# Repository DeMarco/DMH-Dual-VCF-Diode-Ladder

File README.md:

# DMH-Dual-VCF-Diode-Ladder
Stereo version of DMH Diode Ladder VCF

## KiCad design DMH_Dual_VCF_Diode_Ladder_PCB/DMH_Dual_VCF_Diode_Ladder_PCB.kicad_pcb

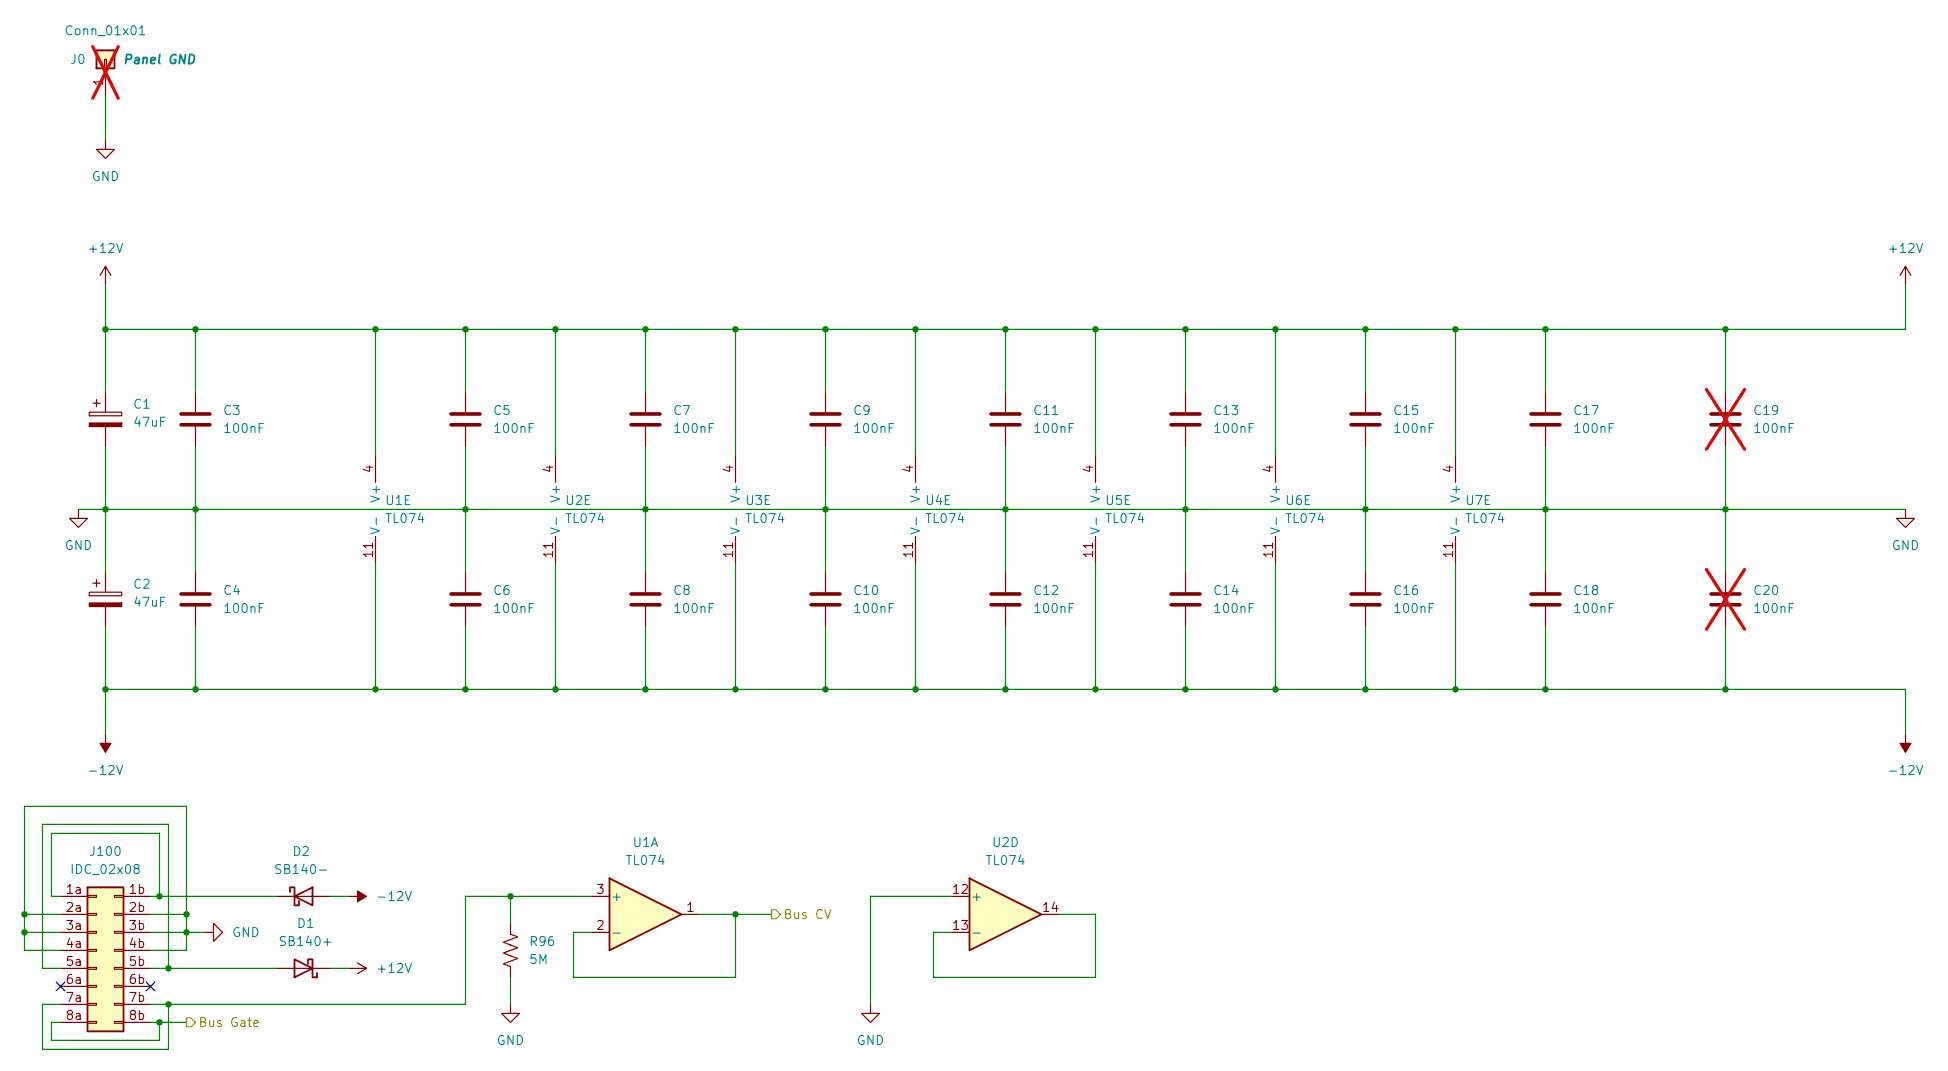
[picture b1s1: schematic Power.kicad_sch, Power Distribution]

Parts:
C1, C2: 47uF; CP_Radial_D5.0mm_P2.00mm
C3, C4, C5, C6, C7, C8, C9, C10, C11, C12, C13, C14, C15, C16, C17, C18: 100nF; C_Disc_D4.3mm_W1.9mm_P5.00mm
C19, C20: 100nF; C_Disc_D4.3mm_W1.9mm_P5.00mm; not fitted
D1: SB140+; D_DO-41_SOD81_P10.16mm_Horizontal
D2: SB140-; D_DO-41_SOD81_P10.16mm_Horizontal
J0: Conn_01x01; PinHeader_1x01_P2.54mm_Vertical; not fitted
J100: IDC_02x08; IDC-Header_2x08_P2.54mm_Vertical_Eurorack
R96: 5M; R_Axial_DIN0207_L6.3mm_D2.5mm_P7.62mm_Horizontal
U1, U2, U3, U4, U5, U6, U7: TL074; DIP-14_W7.62mm_Socket

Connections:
+12V: C1.1, C3.1, C5.1, C7.1, C9.1, C11.1, C13.1, C15.1, C17.1, C19.1, D1.1 (K), U1.4 (V+), U2.4 (V+), U3.4 (V+), U4.4 (V+), U5.4 (V+), U6.4 (V+), U7.4 (V+); also elsewhere on the board
-12V: C2.2, C4.2, C6.2, C8.2, C10.2, C12.2, C14.2, C16.2, C18.2, C20.2, D2.2 (A), U1.11 (V-), U2.11 (V-), U3.11 (V-), U4.11 (V-), U5.11 (V-), U6.11 (V-), U7.11 (V-); also elsewhere on the board
/CV Processing/Bus CV A Input: U1.1, U1.2 (-); also elsewhere on the board
/Power/Bus Gate: J100.8a, J100.8b
GND: C1.2, C2.1, C3.2, C4.1, C5.2, C6.1, C7.2, C8.1, C9.2, C10.1, C11.2, C12.1, C13.2, C14.1, C15.2, C16.1, C17.2, C18.1, C19.2, C20.1, J0.1, J100.2a, J100.2b, J100.3a, J100.3b, J100.4a, J100.4b, R96.2, U2.12 (+); also elsewhere on the board
unnamed: D1.2 (A), J100.5a, J100.5b
unnamed: D2.1 (K), J100.1a, J100.1b
unnamed: J100.7a, J100.7b, R96.1, U1.3 (+)
unnamed: U2.13 (-), U2.14

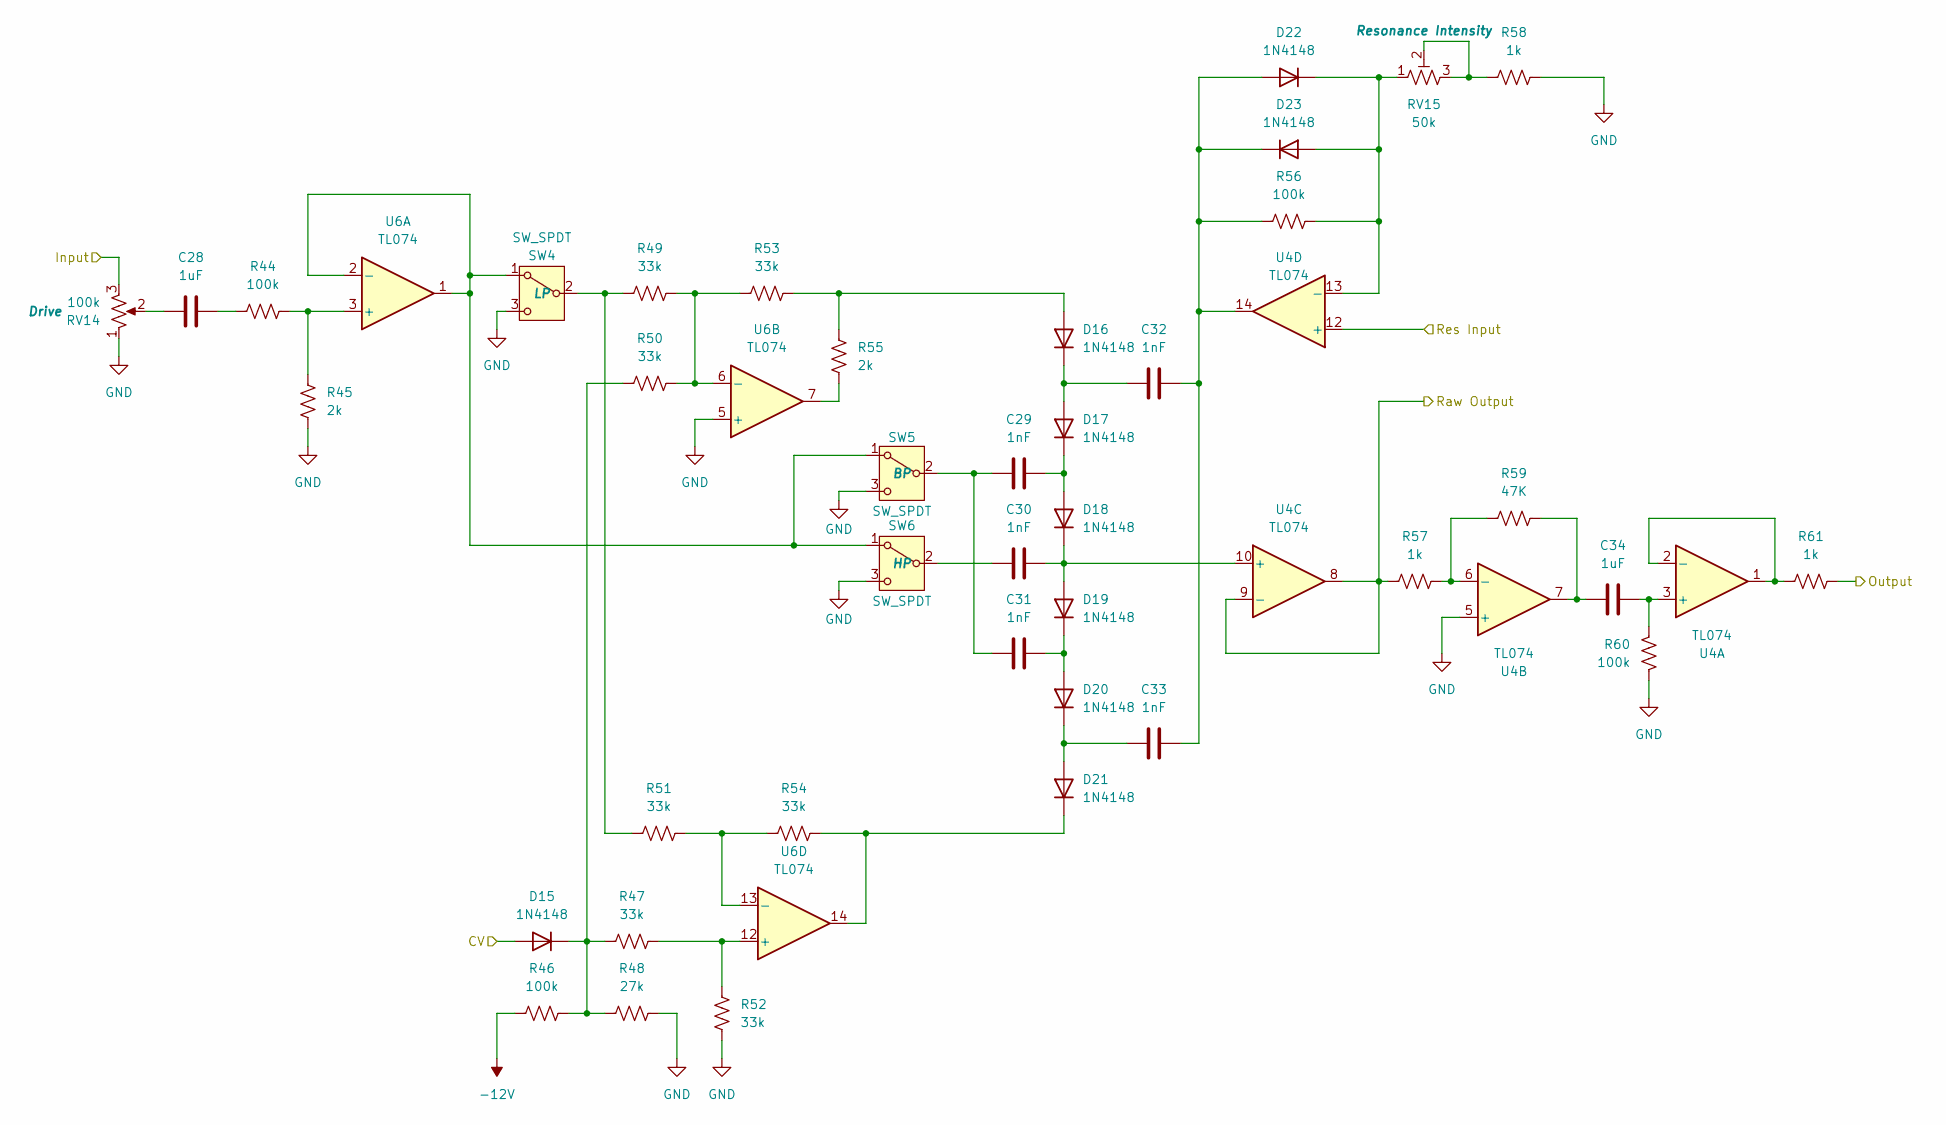
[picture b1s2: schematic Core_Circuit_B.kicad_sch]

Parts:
C28, C34: 1uF; C_Disc_D4.3mm_W1.9mm_P5.00mm
C29, C30, C31, C32, C33: 1nF; C_Disc_D4.3mm_W1.9mm_P5.00mm
D15, D16, D17, D18, D19, D20, D21, D22, D23: 1N4148; D_DO-35_SOD27_P7.62mm_Horizontal
R44, R46, R56, R60: 100k; R_Axial_DIN0207_L6.3mm_D2.5mm_P7.62mm_Horizontal
R45, R55: 2k; R_Axial_DIN0207_L6.3mm_D2.5mm_P7.62mm_Horizontal
R47, R49, R50, R51, R52, R53, R54: 33k; R_Axial_DIN0207_L6.3mm_D2.5mm_P7.62mm_Horizontal
R48: 27k; R_Axial_DIN0207_L6.3mm_D2.5mm_P7.62mm_Horizontal
R57, R58, R61: 1k; R_Axial_DIN0207_L6.3mm_D2.5mm_P7.62mm_Horizontal
R59: 47K; R_Axial_DIN0207_L6.3mm_D2.5mm_P7.62mm_Horizontal
RV14: 100k; Potentiometer_Alpha_RD901F-40-00D_Single_Vertical
RV15: 50k; Potentiometer_Bourns_3296W_Vertical
SW4, SW5, SW6: SW_SPDT; Toggle_Switch_TE
U4, U6: TL074; DIP-14_W7.62mm_Socket

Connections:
-12V: R46.1; also elsewhere on the board
/CV Processing/Link Switch: D15.2 (A); also elsewhere on the board
/Core Circuit B/Input: RV14.3; also elsewhere on the board
/Core Circuit B/Output: R61.2; also elsewhere on the board
/Core Circuit B/Raw Output: R57.1, U4.8, U4.9 (-); also elsewhere on the board
/Core Circuit B/Res Input: U4.12 (+); also elsewhere on the board
GND: R45.1, R48.2, R52.1, R58.2, R60.1, RV14.1, SW4.3 (C), SW5.3 (C), SW6.3 (C), U4.5 (+), U6.5 (+); also elsewhere on the board
unnamed: C28.1, RV14.2
unnamed: C28.2, R44.1
unnamed: C34.1, R59.2, U4.7
unnamed: D15.1 (K), R46.2, R47.1, R48.1, R50.1
unnamed: D16.2 (A), R53.2, R55.2
unnamed: C32.1, D16.1 (K), D17.2 (A)
unnamed: C29.2, D17.1 (K), D18.2 (A)
unnamed: C30.2, D18.1 (K), D19.2 (A), U4.10 (+)
unnamed: C31.2, D19.1 (K), D20.2 (A)
unnamed: C33.1, D20.1 (K), D21.2 (A)
unnamed: D21.1 (K), R54.2, U6.14
unnamed: C32.2, C33.2, D22.2 (A), D23.1 (K), R56.1, U4.14
unnamed: D22.1 (K), D23.2 (A), R56.2, RV15.1, U4.13 (-)
unnamed: R55.1, U6.7
unnamed: R58.1, RV15.2, RV15.3
unnamed: SW4.1 (A), SW5.1 (A), SW6.1 (A), U6.1, U6.2 (-)
unnamed: R49.1, R51.1, SW4.2 (B)
unnamed: C29.1, C31.1, SW5.2 (B)
unnamed: C30.1, SW6.2 (B)
unnamed: C34.2, R60.2, U4.3 (+)
unnamed: R61.1, U4.1, U4.2 (-)
unnamed: R57.2, R59.1, U4.6 (-)
unnamed: R44.2, R45.2, U6.3 (+)
unnamed: R49.2, R50.2, R53.1, U6.6 (-)
unnamed: R47.2, R52.2, U6.12 (+)
unnamed: R51.2, R54.1, U6.13 (-)

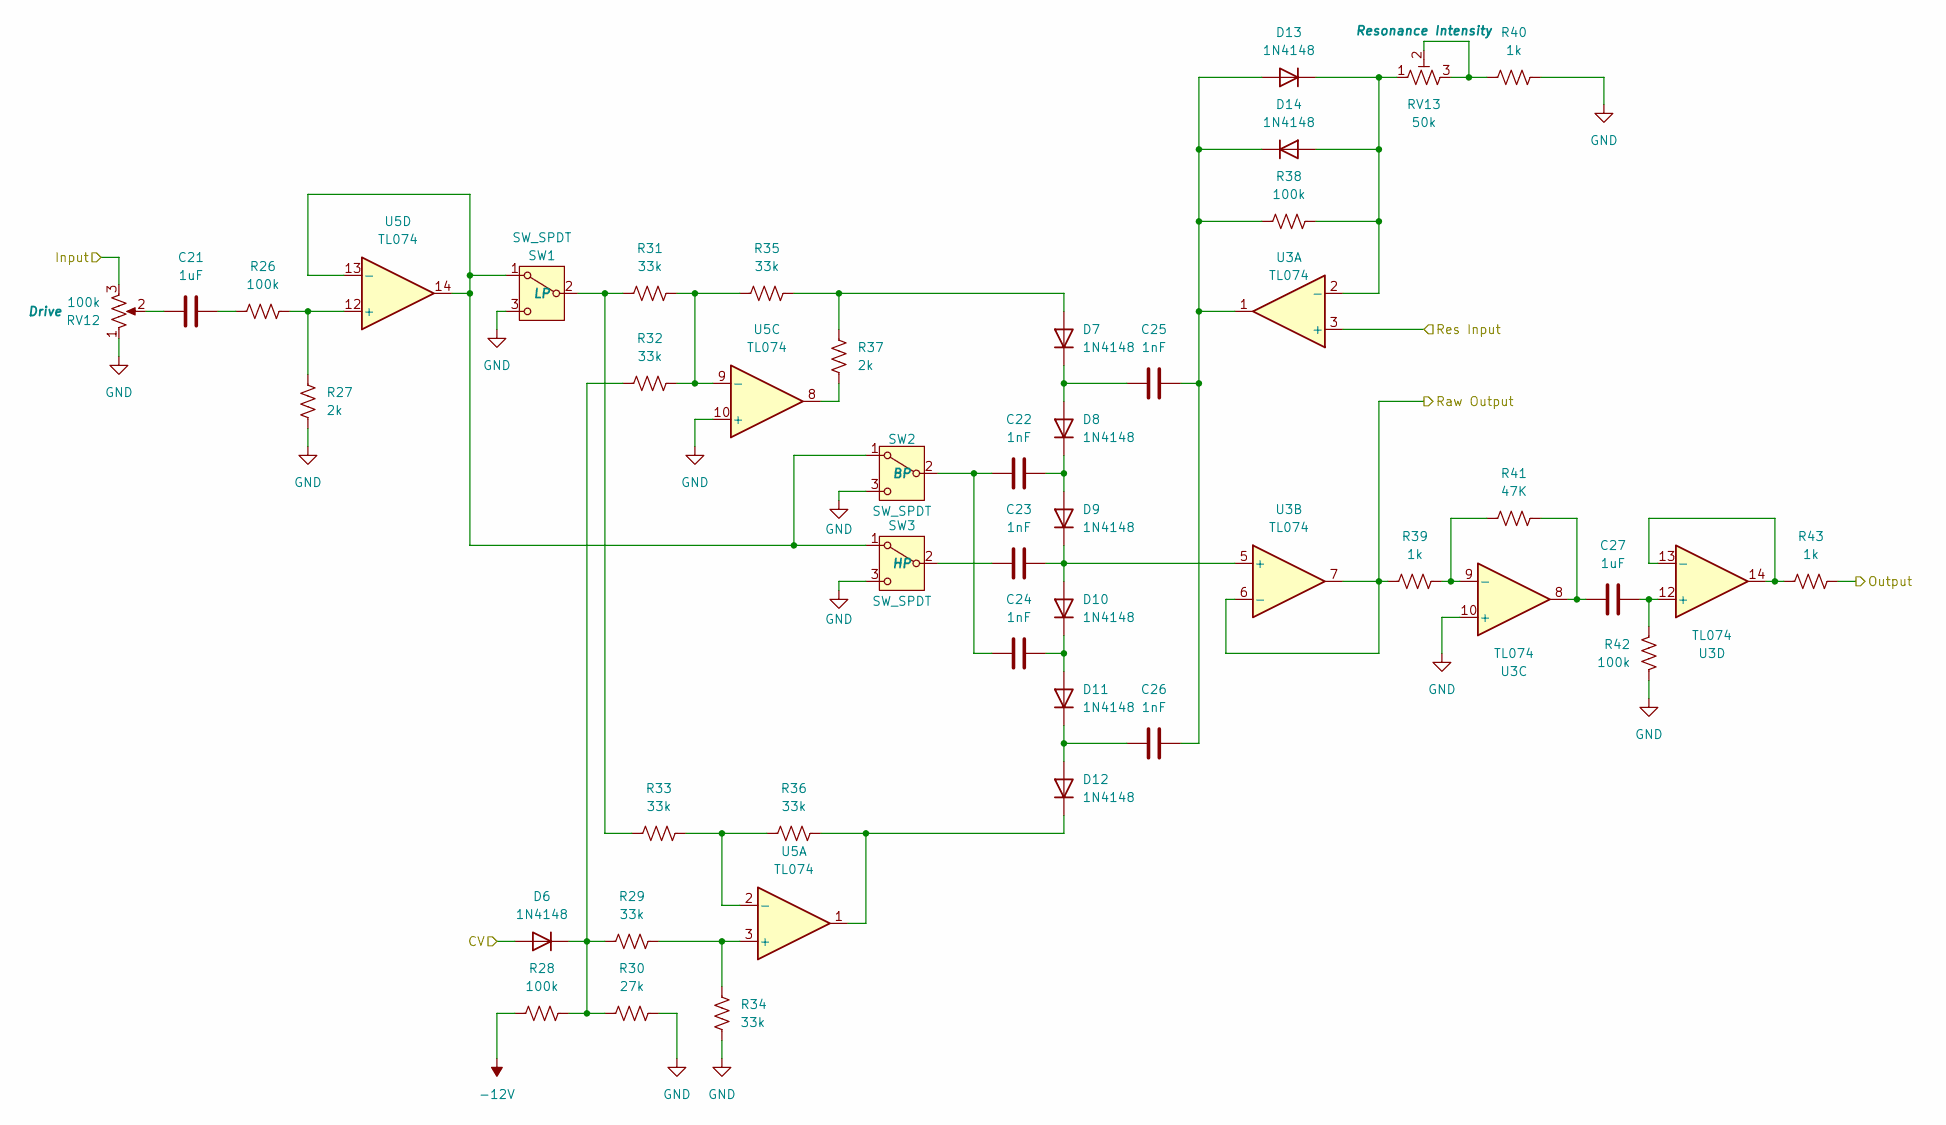
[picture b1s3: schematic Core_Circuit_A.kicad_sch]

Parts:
C21, C27: 1uF; C_Disc_D4.3mm_W1.9mm_P5.00mm
C22, C23, C24, C25, C26: 1nF; C_Disc_D4.3mm_W1.9mm_P5.00mm
D6, D7, D8, D9, D10, D11, D12, D13, D14: 1N4148; D_DO-35_SOD27_P7.62mm_Horizontal
R26, R28, R38, R42: 100k; R_Axial_DIN0207_L6.3mm_D2.5mm_P7.62mm_Horizontal
R27, R37: 2k; R_Axial_DIN0207_L6.3mm_D2.5mm_P7.62mm_Horizontal
R29, R31, R32, R33, R34, R35, R36: 33k; R_Axial_DIN0207_L6.3mm_D2.5mm_P7.62mm_Horizontal
R30: 27k; R_Axial_DIN0207_L6.3mm_D2.5mm_P7.62mm_Horizontal
R39, R40, R43: 1k; R_Axial_DIN0207_L6.3mm_D2.5mm_P7.62mm_Horizontal
R41: 47K; R_Axial_DIN0207_L6.3mm_D2.5mm_P7.62mm_Horizontal
RV12: 100k; Potentiometer_Alpha_RD901F-40-00D_Single_Vertical
RV13: 50k; Potentiometer_Bourns_3296W_Vertical
SW1, SW2, SW3: SW_SPDT; Toggle_Switch_TE
U3, U5: TL074; DIP-14_W7.62mm_Socket

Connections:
-12V: R28.1; also elsewhere on the board
/CV Processing/CV A: D6.2 (A); also elsewhere on the board
/Core Circuit A/Input: RV12.3; also elsewhere on the board
/Core Circuit A/Output: R43.2; also elsewhere on the board
/Core Circuit A/Raw Output: R39.1, U3.6 (-), U3.7; also elsewhere on the board
/Core Circuit A/Res Input: U3.3 (+); also elsewhere on the board
GND: R27.1, R30.2, R34.1, R40.2, R42.1, RV12.1, SW1.3 (C), SW2.3 (C), SW3.3 (C), U3.10 (+), U5.10 (+); also elsewhere on the board
unnamed: C21.1, RV12.2
unnamed: C21.2, R26.1
unnamed: C27.1, R41.2, U3.8
unnamed: D6.1 (K), R28.2, R29.1, R30.1, R32.1
unnamed: D7.2 (A), R35.2, R37.2
unnamed: C25.1, D7.1 (K), D8.2 (A)
unnamed: C22.2, D8.1 (K), D9.2 (A)
unnamed: C23.2, D9.1 (K), D10.2 (A), U3.5 (+)
unnamed: C24.2, D10.1 (K), D11.2 (A)
unnamed: C26.1, D11.1 (K), D12.2 (A)
unnamed: D12.1 (K), R36.2, U5.1
unnamed: C25.2, C26.2, D13.2 (A), D14.1 (K), R38.1, U3.1
unnamed: D13.1 (K), D14.2 (A), R38.2, RV13.1, U3.2 (-)
unnamed: R37.1, U5.8
unnamed: R40.1, RV13.2, RV13.3
unnamed: SW1.1 (A), SW2.1 (A), SW3.1 (A), U5.13 (-), U5.14
unnamed: R31.1, R33.1, SW1.2 (B)
unnamed: C22.1, C24.1, SW2.2 (B)
unnamed: C23.1, SW3.2 (B)
unnamed: R39.2, R41.1, U3.9 (-)
unnamed: C27.2, R42.2, U3.12 (+)
unnamed: R43.1, U3.13 (-), U3.14
unnamed: R29.2, R34.2, U5.3 (+)
unnamed: R33.2, R36.1, U5.2 (-)
unnamed: R31.2, R32.2, R35.1, U5.9 (-)
unnamed: R26.2, R27.2, U5.12 (+)

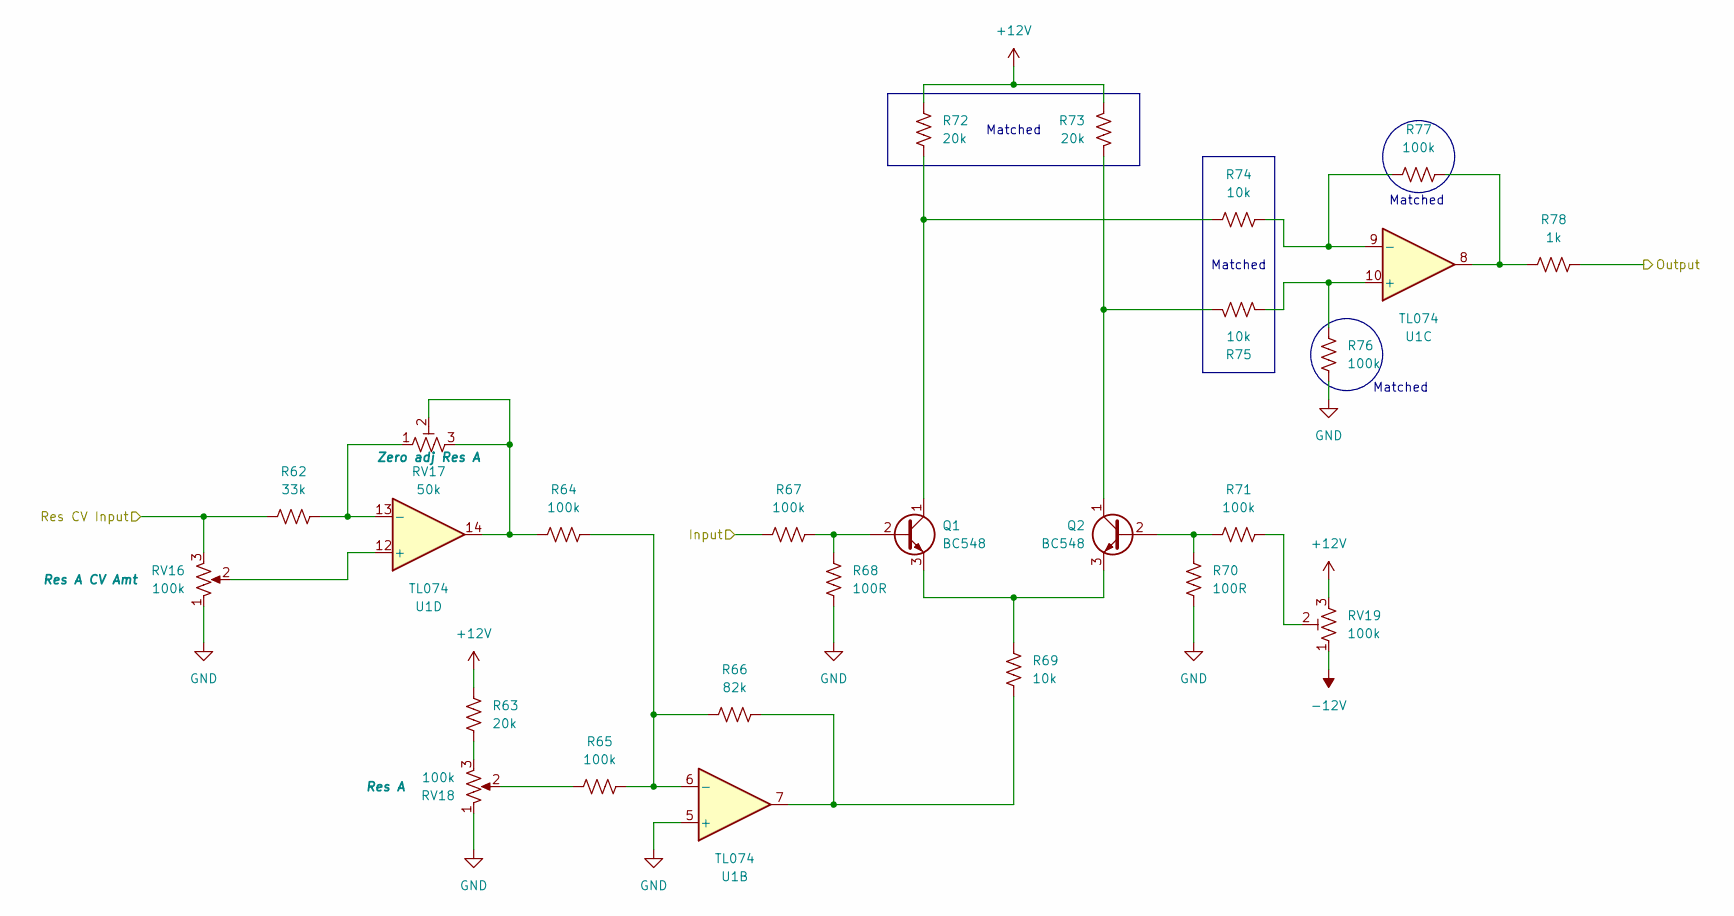
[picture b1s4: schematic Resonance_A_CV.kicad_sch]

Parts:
Q1, Q2: BC548; TO-92L_Inline_Wide
R62: 33k; R_Axial_DIN0207_L6.3mm_D2.5mm_P7.62mm_Horizontal
R63, R72, R73: 20k; R_Axial_DIN0207_L6.3mm_D2.5mm_P7.62mm_Horizontal
R64, R65, R67, R71, R76, R77: 100k; R_Axial_DIN0207_L6.3mm_D2.5mm_P7.62mm_Horizontal
R66: 82k; R_Axial_DIN0207_L6.3mm_D2.5mm_P7.62mm_Horizontal
R68, R70: 100R; R_Axial_DIN0207_L6.3mm_D2.5mm_P7.62mm_Horizontal
R69, R74, R75: 10k; R_Axial_DIN0207_L6.3mm_D2.5mm_P7.62mm_Horizontal
R78: 1k; R_Axial_DIN0207_L6.3mm_D2.5mm_P7.62mm_Horizontal
RV16: 100k; Potentiometer_TT_P110KH1
RV17: 50k; Potentiometer_Bourns_3296W_Vertical
RV18: 100k; Potentiometer_Alpha_RD901F-40-00D_Single_Vertical
RV19: 100k; Potentiometer_Bourns_3296W_Vertical
U1: TL074; DIP-14_W7.62mm_Socket

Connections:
+12V: R63.2, R72.2, R73.2, RV19.3; also elsewhere on the board
-12V: RV19.1; also elsewhere on the board
/Core Circuit A/Raw Output: R67.2; also elsewhere on the board
/Core Circuit A/Res Input: R78.1; also elsewhere on the board
/Inputs and Outputs A/Res CV Jack: R62.1, RV16.3; also elsewhere on the board
GND: R68.1, R70.1, R76.2, RV16.1, RV18.1, U1.5 (+); also elsewhere on the board
unnamed: Q1.2 (B), R67.1, R68.2
unnamed: Q1.1 (C), R72.1, R74.2
unnamed: Q1.3 (E), Q2.3 (E), R69.2
unnamed: Q2.2 (B), R70.2, R71.2
unnamed: Q2.1 (C), R73.1, R75.2
unnamed: R63.1, RV18.3
unnamed: R64.1, RV17.2, RV17.3, U1.14
unnamed: R65.1, RV18.2
unnamed: R66.2, R69.1, U1.7
unnamed: R71.1, RV19.2
unnamed: R77.1, R78.2, U1.8
unnamed: R64.2, R65.2, R66.1, U1.6 (-)
unnamed: R75.1, R76.1, U1.10 (+)
unnamed: R74.1, R77.2, U1.9 (-)
unnamed: RV16.2, U1.12 (+)
unnamed: R62.2, RV17.1, U1.13 (-)

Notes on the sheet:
Matched

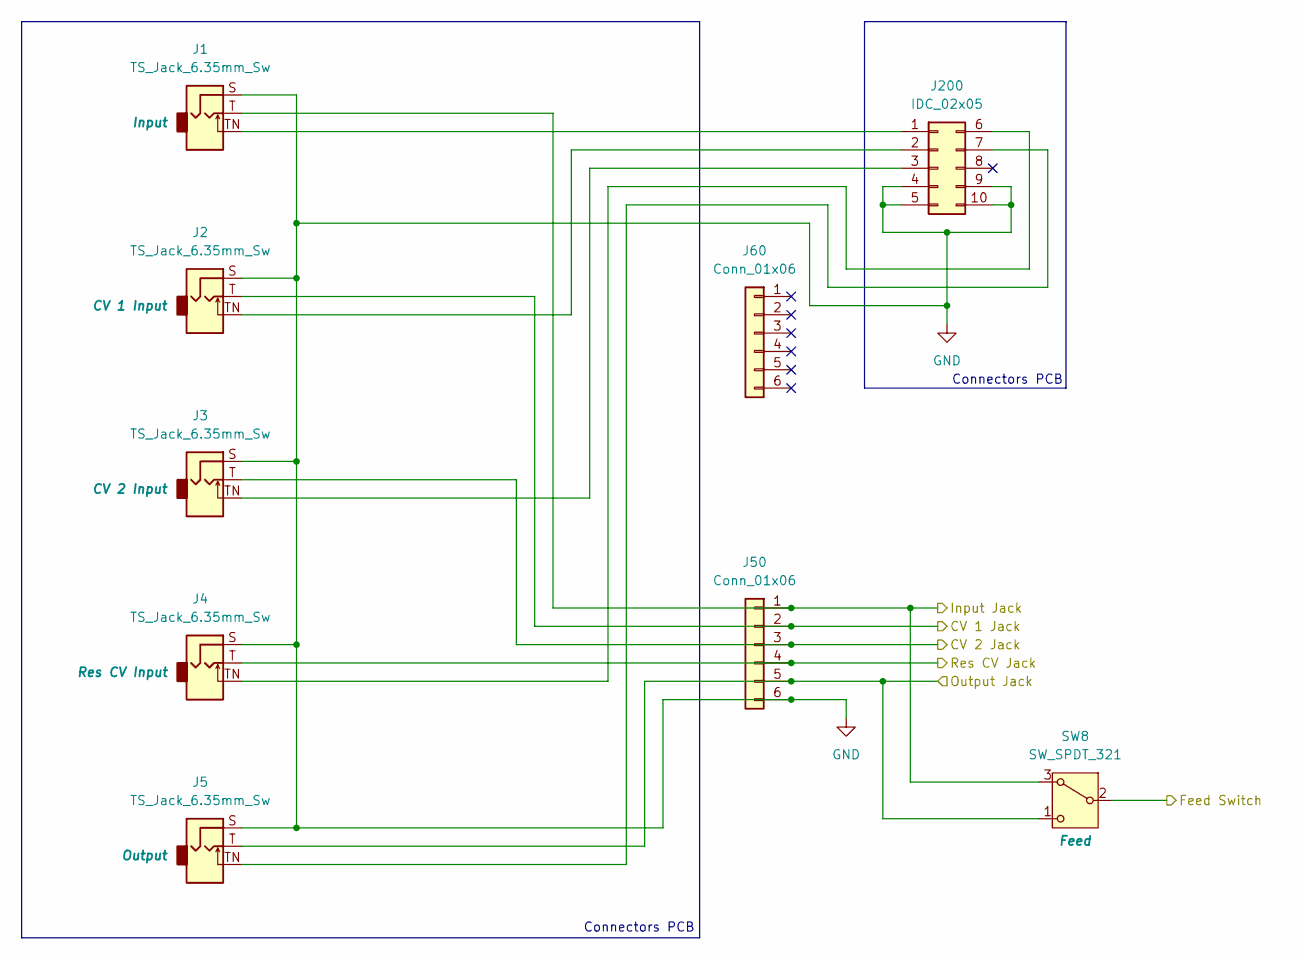
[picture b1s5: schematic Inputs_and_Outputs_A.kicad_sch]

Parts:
J1, J2, J3, J4, J5: TS_Jack_6.35mm_Sw; CUI_MJ-63052A
J50, J60: Conn_01x06; PinSocket_1x06_P2.54mm_Vertical
J200: IDC_02x05; IDC-Header_2x05_P2.54mm_Vertical_BackBone
SW8: SW_SPDT_321; Toggle_Switch_TE

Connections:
/CV Processing/CV1 A Input: J2.T, J50.2; also elsewhere on the board
/CV Processing/CV2 A Input: J3.T, J50.3; also elsewhere on the board
/Core Circuit A/Input: J1.T, J50.1, SW8.3 (A); also elsewhere on the board
/Core Circuit A/Output: J5.T, J50.5, SW8.1 (C); also elsewhere on the board
/Inputs and Outputs A/Feed Switch: SW8.2 (B); also elsewhere on the board
/Inputs and Outputs A/Res CV Jack: J4.T, J50.4; also elsewhere on the board
GND: J1.S, J2.S, J3.S, J4.S, J5.S, J50.6, J200.4, J200.5, J200.9, J200.10; also elsewhere on the board
unnamed: J1.TN, J200.1
unnamed: J2.TN, J200.2
unnamed: J3.TN, J200.3
unnamed: J4.TN, J200.6
unnamed: J5.TN, J200.7

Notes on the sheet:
Connectors PCB

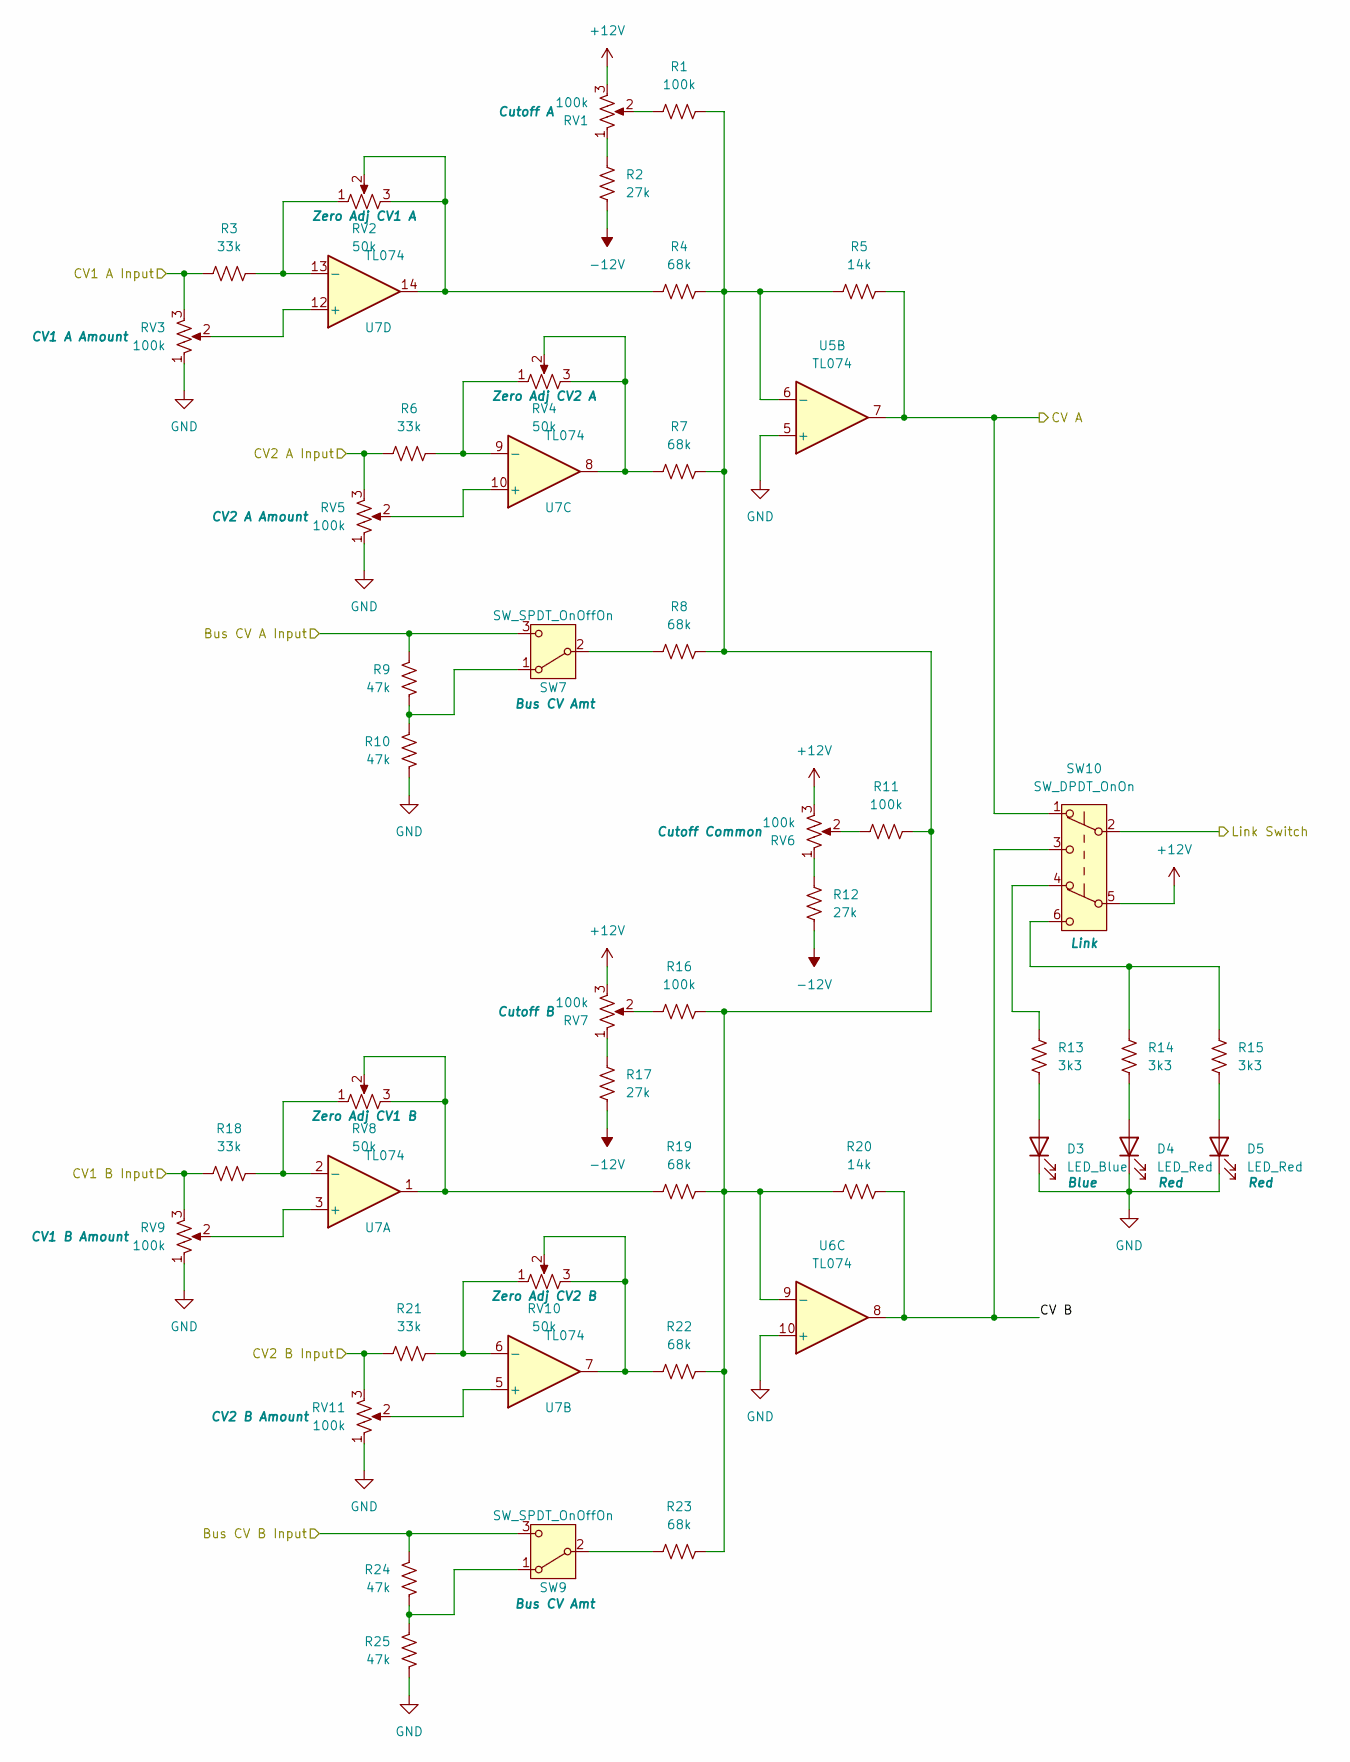
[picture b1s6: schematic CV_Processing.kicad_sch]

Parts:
D3: LED_Blue; LED_D3.0mm
D4, D5: LED_Red; LED_D3.0mm
R1, R11, R16: 100k; R_Axial_DIN0207_L6.3mm_D2.5mm_P7.62mm_Horizontal
R2, R12, R17: 27k; R_Axial_DIN0207_L6.3mm_D2.5mm_P7.62mm_Horizontal
R3, R6, R18, R21: 33k; R_Axial_DIN0207_L6.3mm_D2.5mm_P7.62mm_Horizontal
R4, R7, R8, R19, R22, R23: 68k; R_Axial_DIN0207_L6.3mm_D2.5mm_P7.62mm_Horizontal
R5, R20: 14k; R_Axial_DIN0207_L6.3mm_D2.5mm_P7.62mm_Horizontal
R9, R10, R24, R25: 47k; R_Axial_DIN0207_L6.3mm_D2.5mm_P7.62mm_Horizontal
R13, R14, R15: 3k3; R_Axial_DIN0207_L6.3mm_D2.5mm_P7.62mm_Horizontal
RV1, RV6, RV7: 100k; Potentiometer_Alpha_RD901F-40-00D_Single_Vertical
RV2, RV4, RV8, RV10: 50k; Potentiometer_Bourns_3296W_Vertical
RV3, RV5, RV9, RV11: 100k; Potentiometer_TT_P110KH1
SW7, SW9: SW_SPDT_OnOffOn; Toggle_Switch_TE
SW10: SW_DPDT_OnOn; Toggle_Switch_2_Poles_TE
U5, U6, U7: TL074; DIP-14_W7.62mm_Socket

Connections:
+12V: RV1.3, RV6.3, RV7.3, SW10.5 (B); also elsewhere on the board
-12V: R2.2, R12.2, R17.2; also elsewhere on the board
/CV Processing/Bus CV A Input: R9.2, R24.2, SW7.3 (C), SW9.3 (C); also elsewhere on the board
/CV Processing/CV1 A Input: R3.1, RV3.3; also elsewhere on the board
/CV Processing/CV1 B Input: R18.1, RV9.3; also elsewhere on the board
/CV Processing/CV2 A Input: R6.1, RV5.3; also elsewhere on the board
/CV Processing/CV2 B Input: R21.1, RV11.3; also elsewhere on the board
/CV Processing/CV A: R5.2, SW10.1 (A), U5.7; also elsewhere on the board
/CV Processing/CV B: R20.2, SW10.3 (C), U6.8
/CV Processing/Link Switch: SW10.2 (B); also elsewhere on the board
GND: D3.1 (K), D4.1 (K), D5.1 (K), R10.1, R25.1, RV3.1, RV5.1, RV9.1, RV11.1, U5.5 (+), U6.10 (+); also elsewhere on the board
unnamed: D3.2 (A), R13.2
unnamed: D4.2 (A), R14.2
unnamed: D5.2 (A), R15.2
unnamed: R1.1, RV1.2
unnamed: R2.1, RV1.1
unnamed: R4.1, RV2.2, RV2.3, U7.14
unnamed: R7.1, RV4.2, RV4.3, U7.8
unnamed: R11.1, RV6.2
unnamed: R12.1, RV6.1
unnamed: R13.1, SW10.4 (A)
unnamed: R14.1, R15.1, SW10.6 (C)
unnamed: R16.1, RV7.2
unnamed: R17.1, RV7.1
unnamed: R19.1, RV8.2, RV8.3, U7.1
unnamed: R22.1, RV10.2, RV10.3, U7.7
unnamed: R9.1, R10.2, SW7.1 (A)
unnamed: R8.2, SW7.2 (B)
unnamed: R24.1, R25.2, SW9.1 (A)
unnamed: R23.2, SW9.2 (B)
unnamed: R1.2, R4.2, R5.1, R7.2, R8.1, R11.2, R16.2, R19.2, R20.1, R22.2, R23.1, U5.6 (-), U6.9 (-)
unnamed: RV9.2, U7.3 (+)
unnamed: R18.2, RV8.1, U7.2 (-)
unnamed: RV11.2, U7.5 (+)
unnamed: R21.2, RV10.1, U7.6 (-)
unnamed: RV5.2, U7.10 (+)
unnamed: R6.2, RV4.1, U7.9 (-)
unnamed: RV3.2, U7.12 (+)
unnamed: R3.2, RV2.1, U7.13 (-)

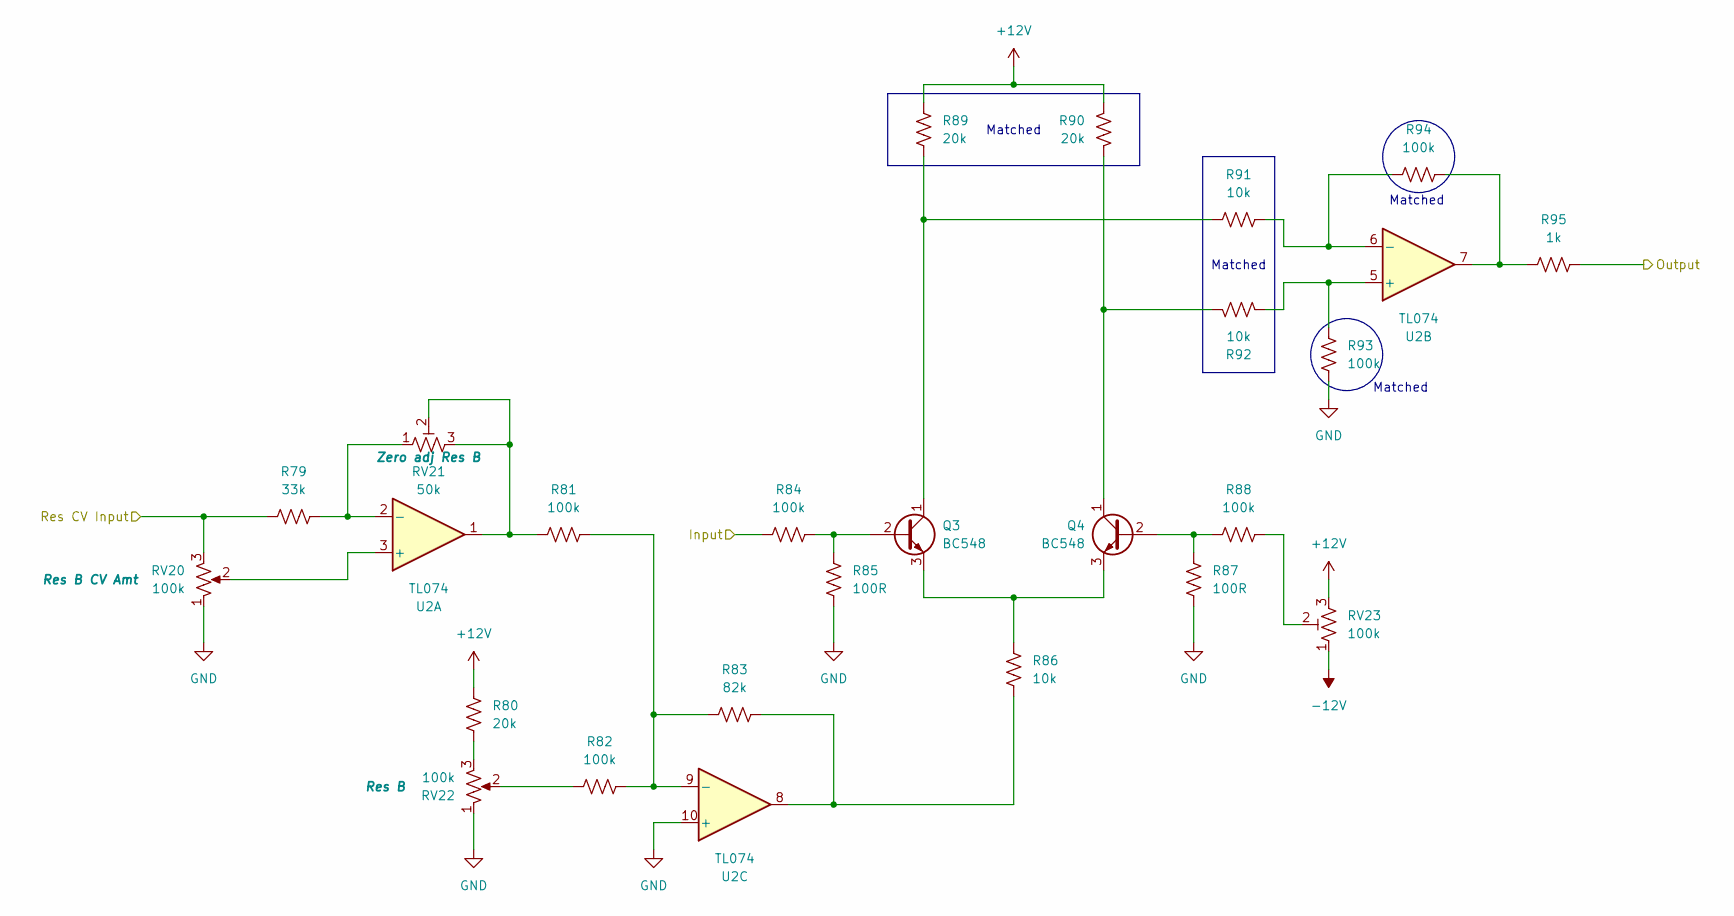
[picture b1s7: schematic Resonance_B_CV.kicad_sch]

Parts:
Q3, Q4: BC548; TO-92L_Inline_Wide
R79: 33k; R_Axial_DIN0207_L6.3mm_D2.5mm_P7.62mm_Horizontal
R80, R89, R90: 20k; R_Axial_DIN0207_L6.3mm_D2.5mm_P7.62mm_Horizontal
R81, R82, R84, R88, R93, R94: 100k; R_Axial_DIN0207_L6.3mm_D2.5mm_P7.62mm_Horizontal
R83: 82k; R_Axial_DIN0207_L6.3mm_D2.5mm_P7.62mm_Horizontal
R85, R87: 100R; R_Axial_DIN0207_L6.3mm_D2.5mm_P7.62mm_Horizontal
R86, R91, R92: 10k; R_Axial_DIN0207_L6.3mm_D2.5mm_P7.62mm_Horizontal
R95: 1k; R_Axial_DIN0207_L6.3mm_D2.5mm_P7.62mm_Horizontal
RV20: 100k; Potentiometer_TT_P110KH1
RV21: 50k; Potentiometer_Bourns_3296W_Vertical
RV22: 100k; Potentiometer_Alpha_RD901F-40-00D_Single_Vertical
RV23: 100k; Potentiometer_Bourns_3296W_Vertical
U2: TL074; DIP-14_W7.62mm_Socket

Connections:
+12V: R80.2, R89.2, R90.2, RV23.3; also elsewhere on the board
-12V: RV23.1; also elsewhere on the board
/Core Circuit B/Raw Output: R84.2; also elsewhere on the board
/Core Circuit B/Res Input: R95.1; also elsewhere on the board
/Inputs and Outputs B/Res CV Jack: R79.1, RV20.3; also elsewhere on the board
GND: R85.1, R87.1, R93.2, RV20.1, RV22.1, U2.10 (+); also elsewhere on the board
unnamed: Q3.2 (B), R84.1, R85.2
unnamed: Q3.1 (C), R89.1, R91.2
unnamed: Q3.3 (E), Q4.3 (E), R86.2
unnamed: Q4.2 (B), R87.2, R88.2
unnamed: Q4.1 (C), R90.1, R92.2
unnamed: R80.1, RV22.3
unnamed: R81.1, RV21.2, RV21.3, U2.1
unnamed: R82.1, RV22.2
unnamed: R83.2, R86.1, U2.8
unnamed: R88.1, RV23.2
unnamed: R94.1, R95.2, U2.7
unnamed: RV20.2, U2.3 (+)
unnamed: R79.2, RV21.1, U2.2 (-)
unnamed: R92.1, R93.1, U2.5 (+)
unnamed: R91.1, R94.2, U2.6 (-)
unnamed: R81.2, R82.2, R83.1, U2.9 (-)

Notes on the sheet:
Matched
